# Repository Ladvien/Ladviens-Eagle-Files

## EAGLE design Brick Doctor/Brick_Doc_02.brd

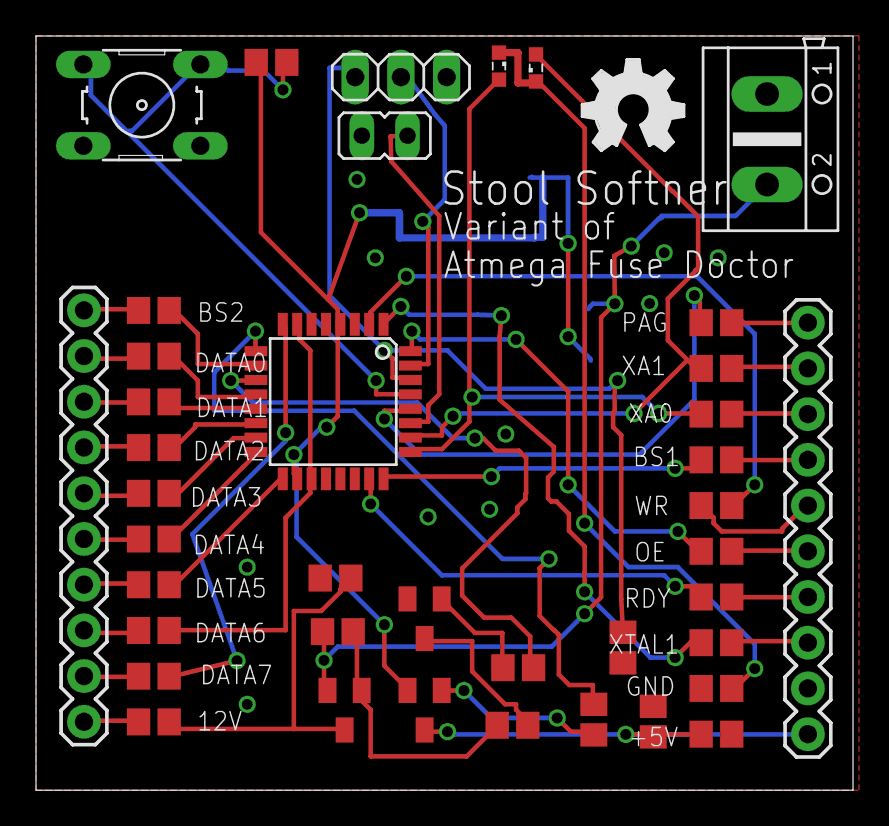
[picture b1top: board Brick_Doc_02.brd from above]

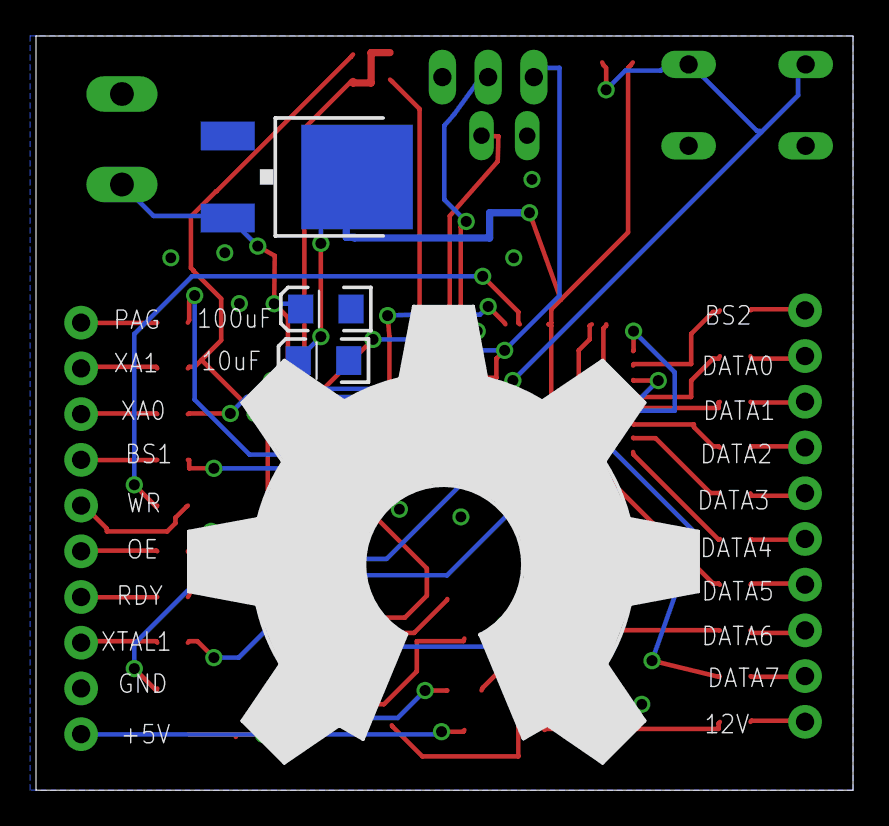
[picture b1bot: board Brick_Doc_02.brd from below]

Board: 2 copper layers, 45.4 x 41.9 mm, 45 parts (4 on the bottom side), 51 nets.

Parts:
C1: 100uF; EIA3216
C2: 10uF; EIA3216
C3: 10nF; C0805
IC1: 7805; V-REG_DPACK
IC2: ATMEGA8-DOC; TQFP32-08
JP1: ERASE; JP1
JP2: RS232; 1X03
JP4, JP5: M10"; 1X10
LED1: red; SML0603
LED2: green; SML0603
Q1, Q2: BC857; SOT23-BEC
R1, R27: 10K; R0805
R2, R7, R8, R9, R10, R11, R12, R13, R14, R15, R16, R17, R18, R19, R20, R21, R22, R23, R24, R26: 1K; R0805
R3, R25: 100; R0805
R4, R6: 4K7; R0805
R5: 330; R0805
S1: START; B3F-10XX
T2: BC847; SOT23
U$1: OSHW_FILLX200_NOTEXT
U$2: OSHW_FILLX1000_NOTEXT
X1: AK500/2

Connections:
+5V: C3.1, JP4.10, Q1.C, R25.2
+12V: JP5.1, R3.2
BS1: JP4.4, R8.2
BS2: JP5.10, R17.2
DATA0: JP5.9, R18.2
DATA1: JP5.8, R19.2
DATA2: JP5.7, R20.2
DATA3: JP5.6, R21.2
DATA4: JP5.5, R22.2
DATA5: JP5.4, R23.2
DATA6: JP5.3, R12.2
DATA7: JP5.2, R13.2
GND: C1.C, C2.C, C3.2, IC1.1, IC2.3, IC2.21, JP1.1, JP2.1, JP4.9, R5.1, R24.1, R25.1, R27.2, S1.3, S1.4, T2.2, X1.1
unnamed: Q1.B, R6.1
unnamed: IC2.12, R18.1
unnamed: IC2.31, JP2.2
unnamed: IC2.28, R11.1
unnamed: IC2.2, R16.1
unnamed: IC2.32, R14.1
unnamed: IC2.30, JP2.3, R27.1
unnamed: R2.2, T2.3
unnamed: IC2.7, IC2.19, R12.1
unnamed: IC2.8, R13.1
unnamed: IC2.11, R4.2
unnamed: IC2.9, R6.2
unnamed: IC2.13, R19.1
unnamed: IC2.14, R20.1
unnamed: IC2.1, R15.1
unnamed: IC2.23, R7.1
unnamed: Q2.C, R3.1, R24.2
unnamed: IC2.15, R21.1
unnamed: IC2.16, R22.1
unnamed: IC2.17, R23.1
unnamed: IC2.10, R17.1
unnamed: R4.1, T2.1
unnamed: IC2.27, JP1.2
unnamed: LED1.C, LED2.C, R5.2
unnamed: Q2.B, R1.2, R2.1
unnamed: IC2.24, R8.1
unnamed: IC2.29, R26.1, S1.1, S1.2
unnamed: IC2.26, LED2.A, R10.1
unnamed: IC2.25, LED1.A, R9.1
OE: JP4.6, R14.2
PAG: JP4.1, R11.2
RDY: JP4.7, R7.2
V+: C1.A, IC1.3, Q2.E, R1.1, X1.2
VCC: C2.A, IC1.4, IC2.4, IC2.18, Q1.E, R26.2
WR: JP4.5, R16.2
XA0: JP4.3, R9.2
XA1: JP4.2, R10.2
XTAL1: JP4.8, R15.2

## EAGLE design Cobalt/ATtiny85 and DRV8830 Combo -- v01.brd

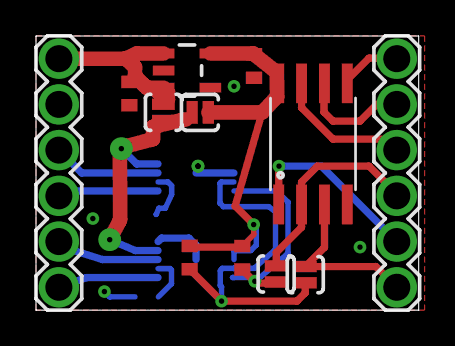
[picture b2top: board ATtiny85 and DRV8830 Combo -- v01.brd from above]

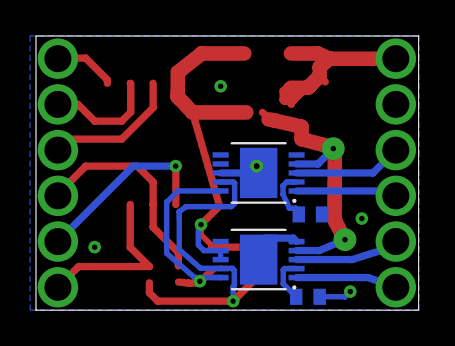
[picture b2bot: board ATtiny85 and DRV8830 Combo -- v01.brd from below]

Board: 2 copper layers, 21.3 x 15.2 mm, 16 parts (4 on the bottom side), 18 nets.

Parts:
1K: R3; R0402
C1, C2: 1uf; C0402
R1, R3: .33; R0402
R2: 1k; R0402
RAW: SOLDERJUMPERNO; SJ_2S-NO
SJ6, SJ7: SOLDERJUMPERNO; SJ_2S-NO
U1: V_REG_LDOSMD; SOT23-5
U2, U3: DRV8830; MSOP-10-GNDPAD
U$1, U$4: 1X6_SHORT_ROUND
U$2: ATTINY85; SO08-EIAJ
VREG: SOLDERJUMPERNO; SJ_2S-NO

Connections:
GND: C1.2, C2.2, R1.1, R3.1, U1.2, U2.5, U2.GND, U3.5, U3.7, U3.8, U3.GND, U$2.4, U$4.2
unnamed: R1.2, U3.2
unnamed: R3.2, U2.2
unnamed: U2.3, U$4.5
unnamed: U2.1, U$4.6
unnamed: U3.1, U$4.4
unnamed: U3.3, U$4.3
PB0: U$1.1, U$2.5
PB1: U$1.2, U$2.6
PB2: U$1.3, U$2.7
PB3: SJ7.2, U$1.4, U$2.2
PB4: SJ6.2, U$1.6, U$2.3
PB5: U$1.5, U$2.1
RAW: C1.1, RAW.1, U1.1, U1.3, U$4.1
SCL: R2.2, SJ7.1, U2.10, U3.10
SDA: 1K.2, SJ6.1, U2.9, U3.9
VCC: RAW.2, U2.4, U3.4, VREG.2
VREG: 1K.1, C2.1, R2.1, U1.5, U2.7, U2.8, U$2.8, VREG.1

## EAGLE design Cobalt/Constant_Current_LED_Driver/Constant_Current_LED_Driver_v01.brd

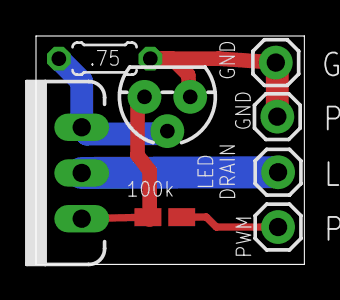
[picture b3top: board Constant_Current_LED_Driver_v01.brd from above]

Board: 2 copper layers, 14.9 x 12.7 mm, 8 parts (0 on the bottom side), 5 nets.

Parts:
GND: M01PTH; 1X01
LED_DRAIN: M01PTH; 1X01
PWM: M01PTH; 1X01
PWM_GND: M01PTH; 1X01
Q1: MOSFET-NCHANNELFQP30N06L; TO220V
Q2: TO-92
R1: 100k; R0805W
R2: .75Ohm; 0204/5

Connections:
FET_SOURCE: Q1.3, Q2.2, R2.1
GND: GND.1, PWM_GND.1, Q2.1, R2.2
LED_DRAIN: LED_DRAIN.1, Q1.2
PWM_A: PWM.1, R1.1
PWM_B: Q1.1, Q2.3, R1.2

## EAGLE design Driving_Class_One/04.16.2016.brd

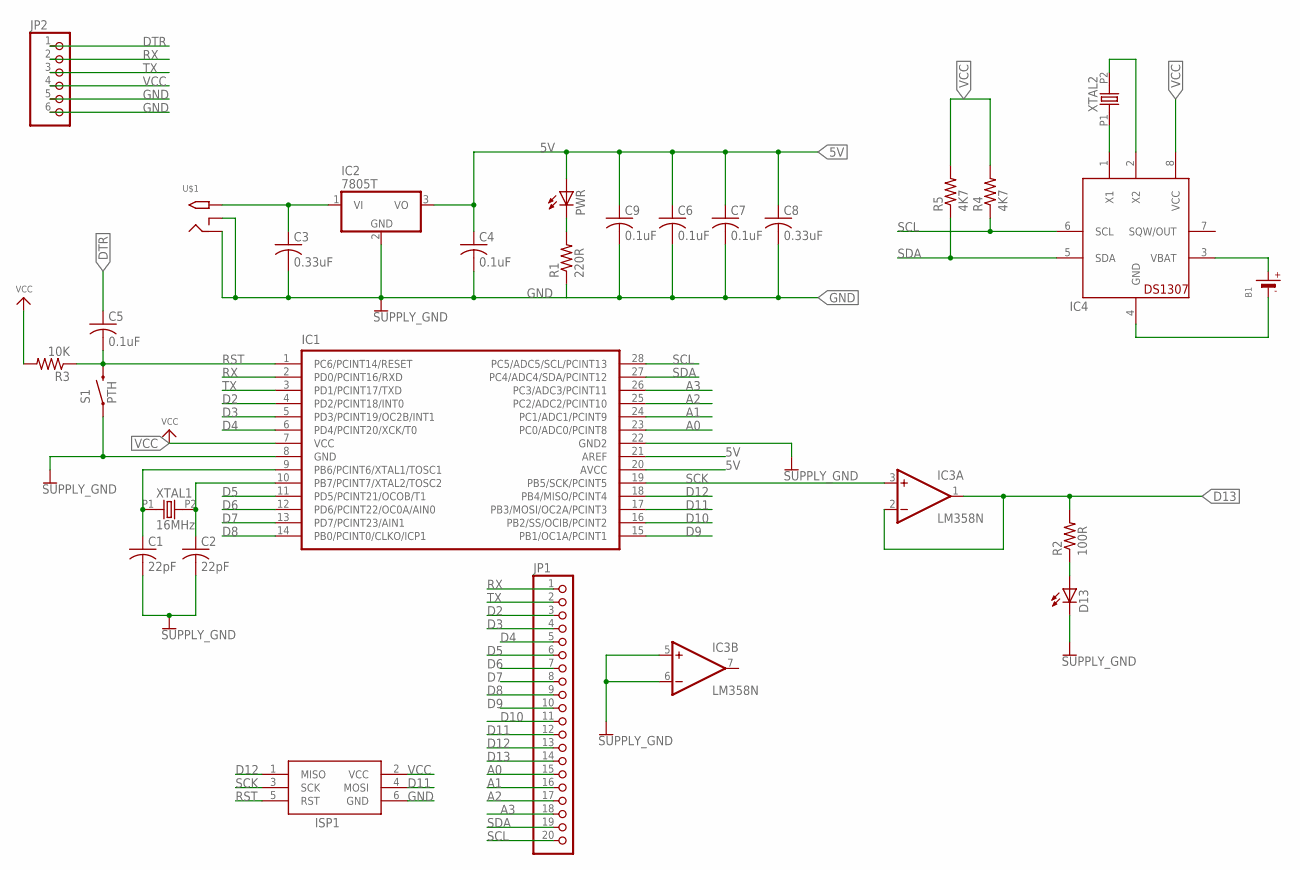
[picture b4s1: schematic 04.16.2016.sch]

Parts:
B1: BATTERYCR2032; CR2032
C1, C2: 22pF; C050-025X075
C3, C8: 0.33uF; C050-025X075
C4, C5, C6, C7, C9: 0.1uF; C050-025X075
D13: LED5MM
IC1: IC_UC_ATMEGA328PDIL; DIL28-N
IC2: 7805T; TO220H
IC3: LM358N; DIL08
IC4: DS1307; DIL08
ISP1: AVRISP-6; AVRISP
JP1: PINHD-1X20-BIG; 1X20-BIG
JP2: PINHD-1X6; 1X06
PWR: LED5MM
R1: 220R; 0207/10
R2: 100R; 0207/10
R3: 10K; 0207/10
R4, R5: 4K7; 0207/10
S1: PTH; TACTILE-PTH
U$1: 2.1MMJACKTHM; PJ-102A
XTAL1: 16MHz; HC-49U-PTH
XTAL2: OSC-XTALTC-26; TC-26

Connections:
5V: C4.1, C6.1, C7.1, C8.1, C9.1, IC1.20 (AVCC), IC1.21 (AREF), IC2.3 (VO), PWR.A
A0: IC1.23 (PC0/ADC0/PCINT8), JP1.15
A1: IC1.24 (PC1/ADC1/PCINT9), JP1.16
A2: IC1.25 (PC2/ADC2/PCINT10), JP1.17
A3: IC1.26 (PC3/ADC3/PCINT11), JP1.18
D2: IC1.4 (PD2/PCINT18/INT0), JP1.3
D3: IC1.5 (PD3/PCINT19/OC2B/INT1), JP1.4
D4: IC1.6 (PD4/PCINT20/XCK/T0), JP1.5
D5: IC1.11 (PD5/PCINT21/OCOB/T1), JP1.6
D6: IC1.12 (PD6/PCINT22/OC0A/AIN0), JP1.7
D7: IC1.13 (PD7/PCINT23/AIN1), JP1.8
D8: IC1.14 (PB0/PCINT0/CLKO/ICP1), JP1.9
D9: IC1.15 (PB1/OC1A/PCINT1), JP1.10
D10: IC1.16 (PB2/SS/OCIB/PCINT2), JP1.11
D11: IC1.17 (PB3/MOSI/OC2A/PCINT3), ISP1.4 (MOSI), JP1.12
D12: IC1.18 (PB4/MISO/PCINT4), ISP1.1 (MISO), JP1.13
D13: IC3.1 (OUT), IC3.2 (-IN), JP1.14, R2.2
DTR: C5.1, JP2.1
GND: C1.2, C2.2, C3.2, C4.2, C6.2, C7.2, C8.2, C9.2, D13.K (C), IC1.8 (GND), IC1.22 (GND2), IC2.2 (GND), IC3.5 (+IN), IC3.6 (-IN), ISP1.6 (GND), JP2.5, JP2.6, R1.1, S1.1, U$1.RING, U$1.RING_SW
unnamed: C1.1, IC1.9 (PB6/PCINT6/XTAL1/TOSC1), XTAL1.P1 (1)
unnamed: C2.1, IC1.10 (PB7/PCINT7/XTAL2/TOSC2), XTAL1.P2 (2)
unnamed: PWR.K (C), R1.2
unnamed: D13.A, R2.1
unnamed: C3.1, IC2.1 (VI), U$1.TIP
unnamed: IC4.1 (X1), XTAL2.P1 (1)
unnamed: IC4.2 (X2), XTAL2.P2 (2)
unnamed: B1.-, IC4.4 (GND)
unnamed: B1.+, IC4.3 (VBAT)
RST: C5.2, IC1.1 (PC6/PCINT14/RESET), ISP1.5 (RST), R3.1, S1.3 (2)
RX: IC1.2 (PD0/PCINT16/RXD), JP1.1, JP2.2
SCK: IC1.19 (PB5/SCK/PCINT5), IC3.3 (+IN), ISP1.3 (SCK)
SCL: IC1.28 (PC5/ADC5/SCL/PCINT13), IC4.6 (SCL), JP1.20, R4.1
SDA: IC1.27 (PC4/ADC4/SDA/PCINT12), IC4.5 (SDA), JP1.19, R5.1
TX: IC1.3 (PD1/PCINT17/TXD), JP1.2, JP2.3
V+: IC3.8 (V+)
V-: IC3.4 (V-)
VCC: IC1.7 (VCC), IC4.8 (VCC), ISP1.2 (VCC), JP2.4, R3.2, R4.2, R5.2

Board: 2 copper layers, 28 parts (1 on the bottom side), 35 nets, no tracks yet.

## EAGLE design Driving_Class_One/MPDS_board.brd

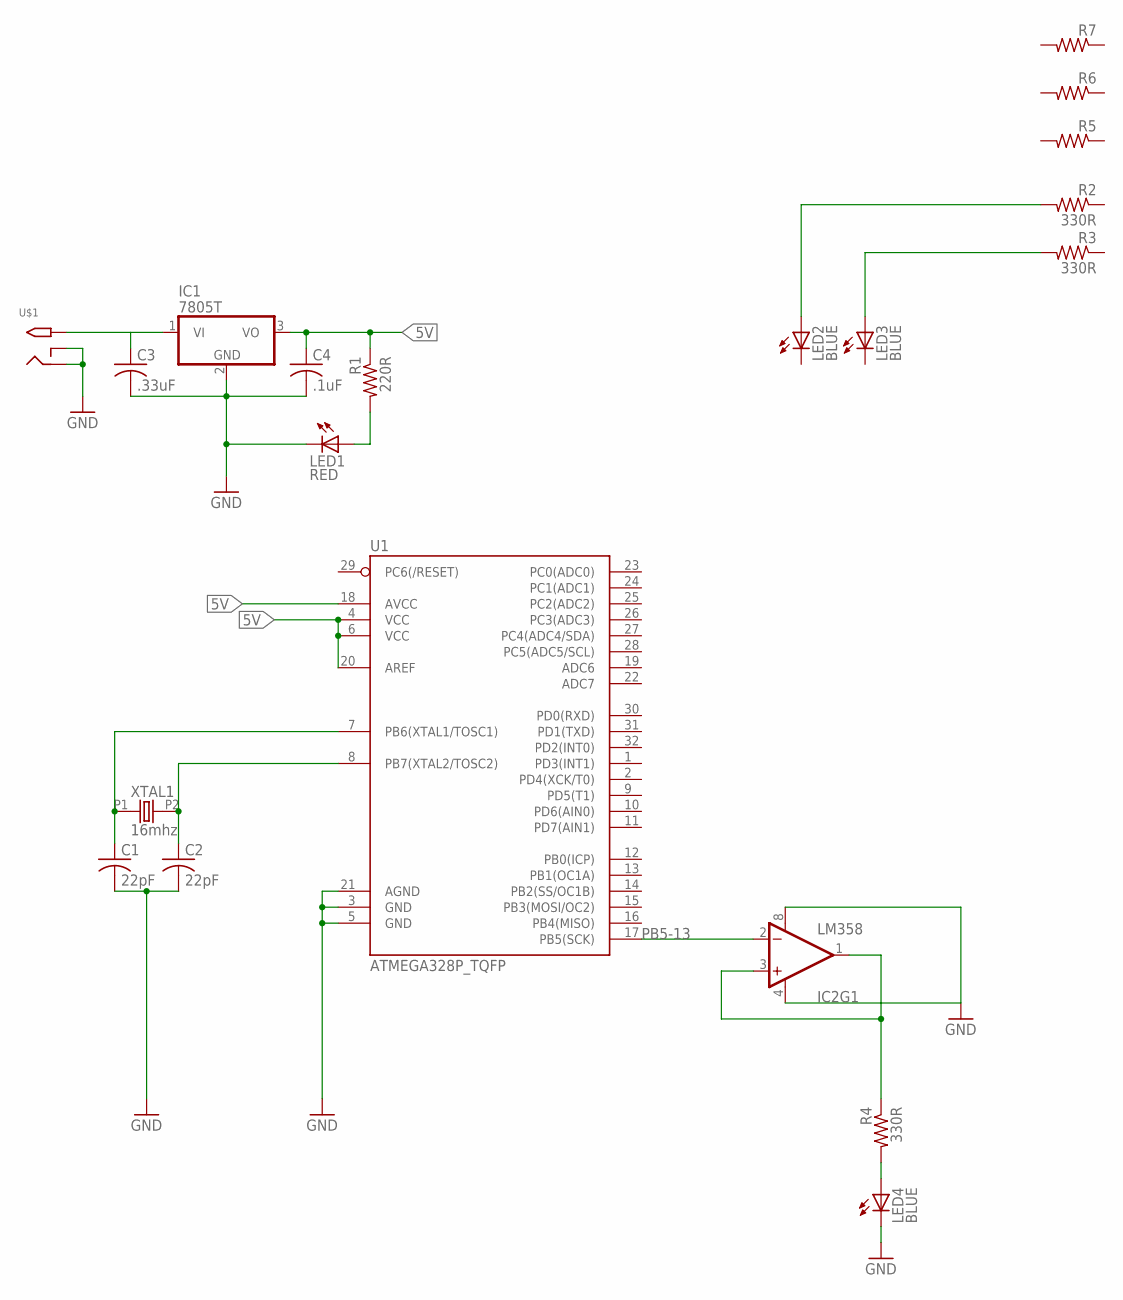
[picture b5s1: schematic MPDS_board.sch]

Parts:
C1, C2: 22pF; C050-025X075
C3: .33uF; C050-025X075
C4: .1uF; C050-025X075
IC1: 7805T; TO220H
IC2: LM358; DIP08
LED1: RED; LED5MM
LED2, LED3, LED4: BLUE; LED5MM
R1: 220R; 0207/10
R2, R3, R4: 330R; 0207/10
R5, R6, R7: R-US_0207/10; 0207/10
U1: ATMEGA328P_TQFP; TQFP32-08
U$1: 2.1MMJACKTHM; PJ-102A
XTAL1: 16mhz; HC-49U-PTH

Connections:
5V: C4.1, IC1.3 (VO), R1.1, U1.4 (VCC), U1.6 (VCC), U1.18 (AVCC), U1.20 (AREF)
GND: C1.2, C2.2, C3.2, C4.2, IC1.2 (GND), IC2.4 (V-), IC2.8 (V+), LED1.K (C), LED4.K (C), U1.3 (GND), U1.5 (GND), U1.21 (AGND), U$1.RING, U$1.RING_SW
unnamed: C1.1, U1.7 (PB6(XTAL1/TOSC1)), XTAL1.P1 (1)
unnamed: C2.1, U1.8 (PB7(XTAL2/TOSC2)), XTAL1.P2 (2)
unnamed: LED4.A, R4.2
unnamed: C3.1, IC1.1 (VI), U$1.TIP
unnamed: LED3.A, R3.2
unnamed: LED2.A, R2.2
unnamed: LED1.A, R1.2
unnamed: IC2.1 (OUT), IC2.3 (+IN), R4.1
PB5-13: IC2.2 (-IN), U1.17 (PB5(SCK))

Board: 2 copper layers, 20 parts (0 on the bottom side), 11 nets, no tracks yet.

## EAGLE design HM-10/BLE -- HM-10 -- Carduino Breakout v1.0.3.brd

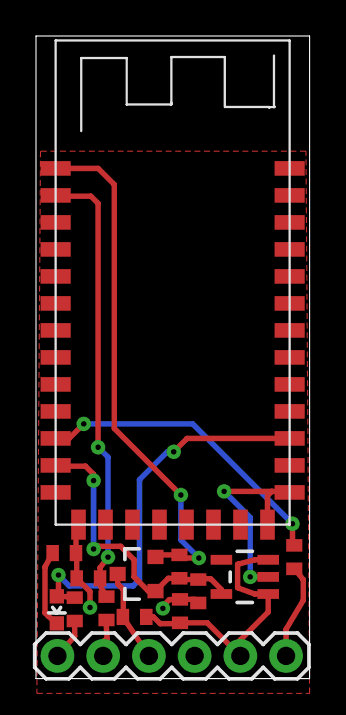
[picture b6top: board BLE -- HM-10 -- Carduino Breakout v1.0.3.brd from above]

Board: 2 copper layers, 15.2 x 35.7 mm, 15 parts (0 on the bottom side), 12 nets.

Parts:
BSS138: MOSFET-NCHANNELSMD; SOT23-3
C1, C2: 1uF; C0402
CONN_LED: LED-0603
JP1: 1X06
R3, R5, R6: 10k; R0402
R4: 20k; R0402
R7: 470; R0402
R8, R9: 10K; R0402
U1: V_REG_LDOSMD; SOT23-5
U$1: BLE-HM-10
U$3: OSHW_FILLX70_NOTEXT

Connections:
3_3V: BSS138.1, C2.1, R6.2, U1.5, U$1.3.3V
5V: C1.1, JP1.5, R5.2, U1.1, U1.3
CONN: JP1.1, R8.1
GND: C1.2, C2.2, JP1.4, R4.2, R7.1, U1.2, U$1.GND1, U$1.GND2, U$1.GND3, U$1.GND4
HVTX->LVRX: R3.2, R4.1, U$1.UART_RX
LVRX->HVTX: BSS138.2, R6.1, U$1.UART_TX
unnamed: CONN_LED.A, R8.2, U$1.PIO1
unnamed: CONN_LED.C, R7.2
RES: R9.1, U$1.RESET
RES_C: JP1.6, R9.2
RX: JP1.2, R3.1
TX: BSS138.3, JP1.3, R5.1

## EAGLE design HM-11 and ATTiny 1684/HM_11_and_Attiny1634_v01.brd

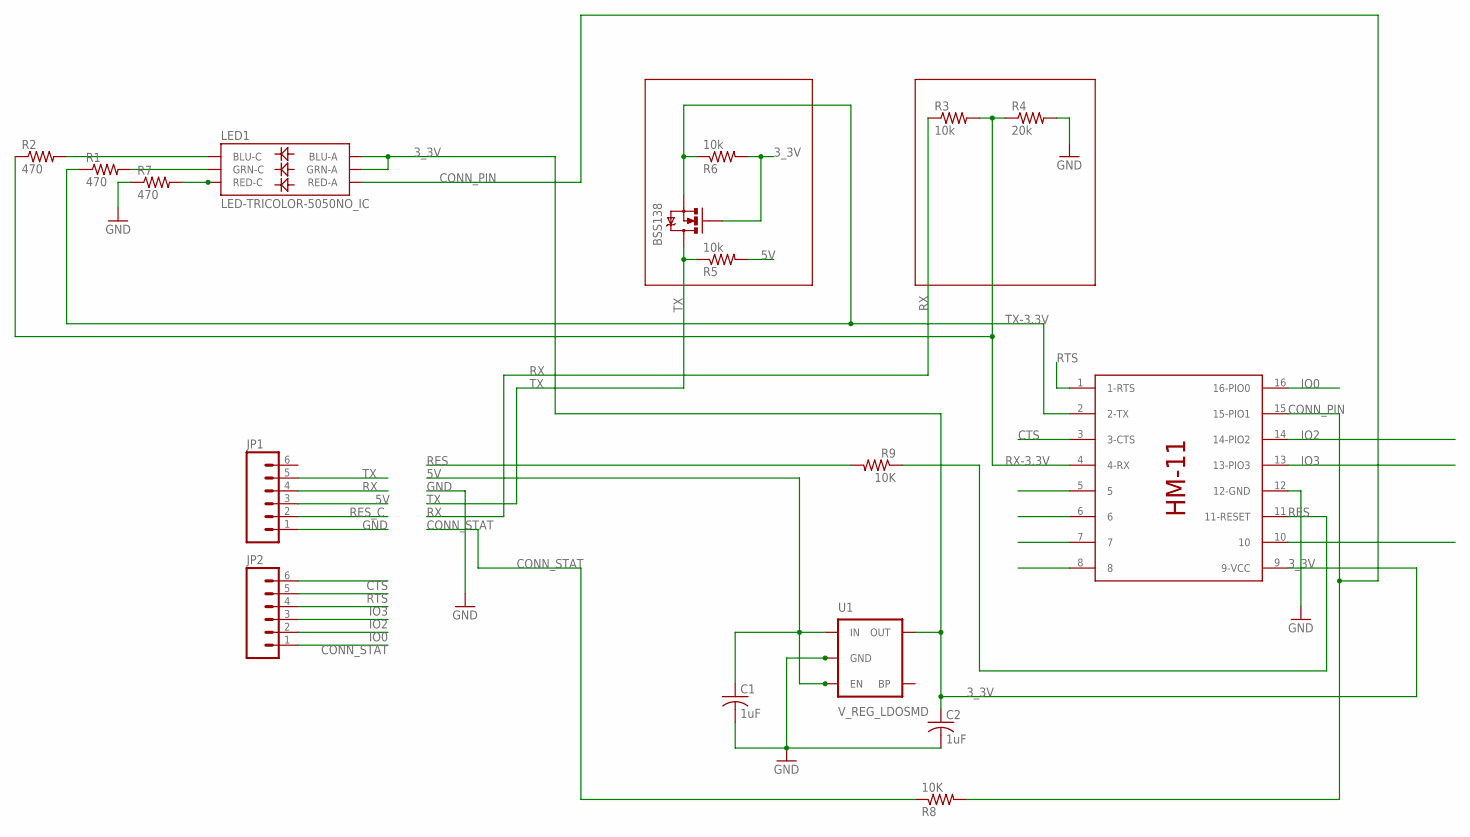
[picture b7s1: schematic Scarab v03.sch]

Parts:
BSS138: MOSFET-NCHANNELSMD; SOT23-3
C1, C2: 1uF; C0402
JP1, JP2: M06LOCK; 1X06_LOCK
LED1: LED-TRICOLOR-5050NO_IC; LED-TRICOLOR-5050
R1, R2, R7: 470; R0402
R3, R5, R6: 10k; R0402
R4: 20k; R0402
R8, R9: 10K; R0402
U1: V_REG_LDOSMD; SOT23-5
U$1: HM-11

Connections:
3_3V: BSS138.1 (G), C2.1, LED1.1 (GRN-A), LED1.3 (BLU-A), R6.2, U1.5 (OUT), U$1.9 (9-VCC)
5V: C1.1, JP1.3, R5.2, U1.1 (IN), U1.3 (EN)
CONN_PIN: LED1.2 (RED-A), R8.2, U$1.15 (15-PIO1)
CONN_STAT: JP2.1, R8.1
CTS: JP2.6, U$1.3 (3-CTS)
GND: C1.2, C2.2, JP1.1, R4.2, R7.1, U1.2 (GND), U$1.12 (12-GND)
IO0: JP2.2, U$1.16 (16-PIO0)
IO2: JP2.3, U$1.14 (14-PIO2)
IO3: JP2.4, U$1.13 (13-PIO3)
unnamed: LED1.6 (GRN-C), R1.2
unnamed: LED1.4 (BLU-C), R2.2
unnamed: LED1.5 (RED-C), R7.2
RES: R9.1, U$1.11 (11-RESET)
RES_C: JP1.2, R9.2
RTS: JP2.5, U$1.1 (1-RTS)
RX: JP1.4, R3.1
RX-3.3V: R2.1, R3.2, R4.1, U$1.4 (4-RX)
TX: BSS138.3 (D), JP1.5, R5.1
TX-3.3V: BSS138.2 (S), R1.1, R6.1, U$1.2 (2-TX)

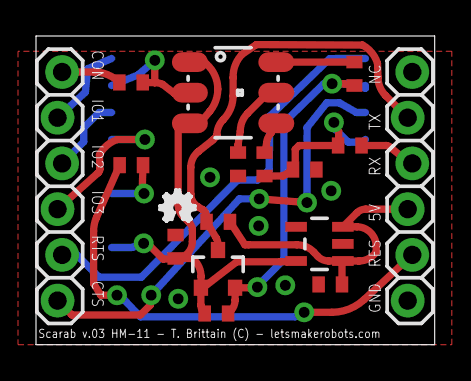
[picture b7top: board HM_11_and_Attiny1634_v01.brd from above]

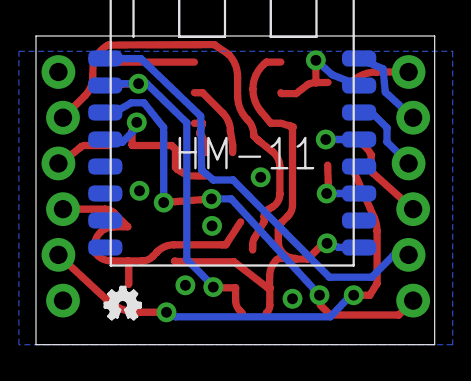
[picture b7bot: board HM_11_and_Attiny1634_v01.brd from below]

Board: 2 copper layers, 22.1 x 17.1 mm, 19 parts (2 on the bottom side), 19 nets.

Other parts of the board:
U$3, U$4: OSHW_FILLX70_NOTEXT

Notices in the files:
parts and their libraries:
SparkFun: Licensing: CC v3.0 Share-Alike You are welcome to use this library for commercial purposes.
SparkFun-Electromechanical: Licensing: Creative Commons ShareAlike 4.0 International - https://creativecommons.org/licenses/by-sa/4.0
